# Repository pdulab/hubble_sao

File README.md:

## Features

The main features of the SAO are :
- An optical sensor : a VEML3328 to provide a 1x1 pixel RGB+IR camera
- An IMU (accel + gyro) : an LSM6DSO, because every good telescope needs to know its orientation (note that only one remaining gyroscope is working correctly on Hubble, so my SAO has the same number of gyroscope, nice !)
- 4 photodiodes : they represent the solar panels of Hubble. I'm using BPW34s (the IR version, to be precise). They are wired to the ADC of the microcontroller.
- An IR LED : to provide a way to send wireless data
- An microcontroller : I used a ATmega328PB

On top of that, there are :

- A standard yellow LED, because an SAO would be nothing without some blinky LEDs
- A button

## License
 Hubble SAO by pdulab is licensed under CC BY-NC-SA 4.0 

 ## Disclaimer
 This is a project for fun. I do not guarantee anything about it.
 The author is not affiliated with the official Hubble Space Telescope project or endorsed by it (or any related organization) in any way whatsoever.

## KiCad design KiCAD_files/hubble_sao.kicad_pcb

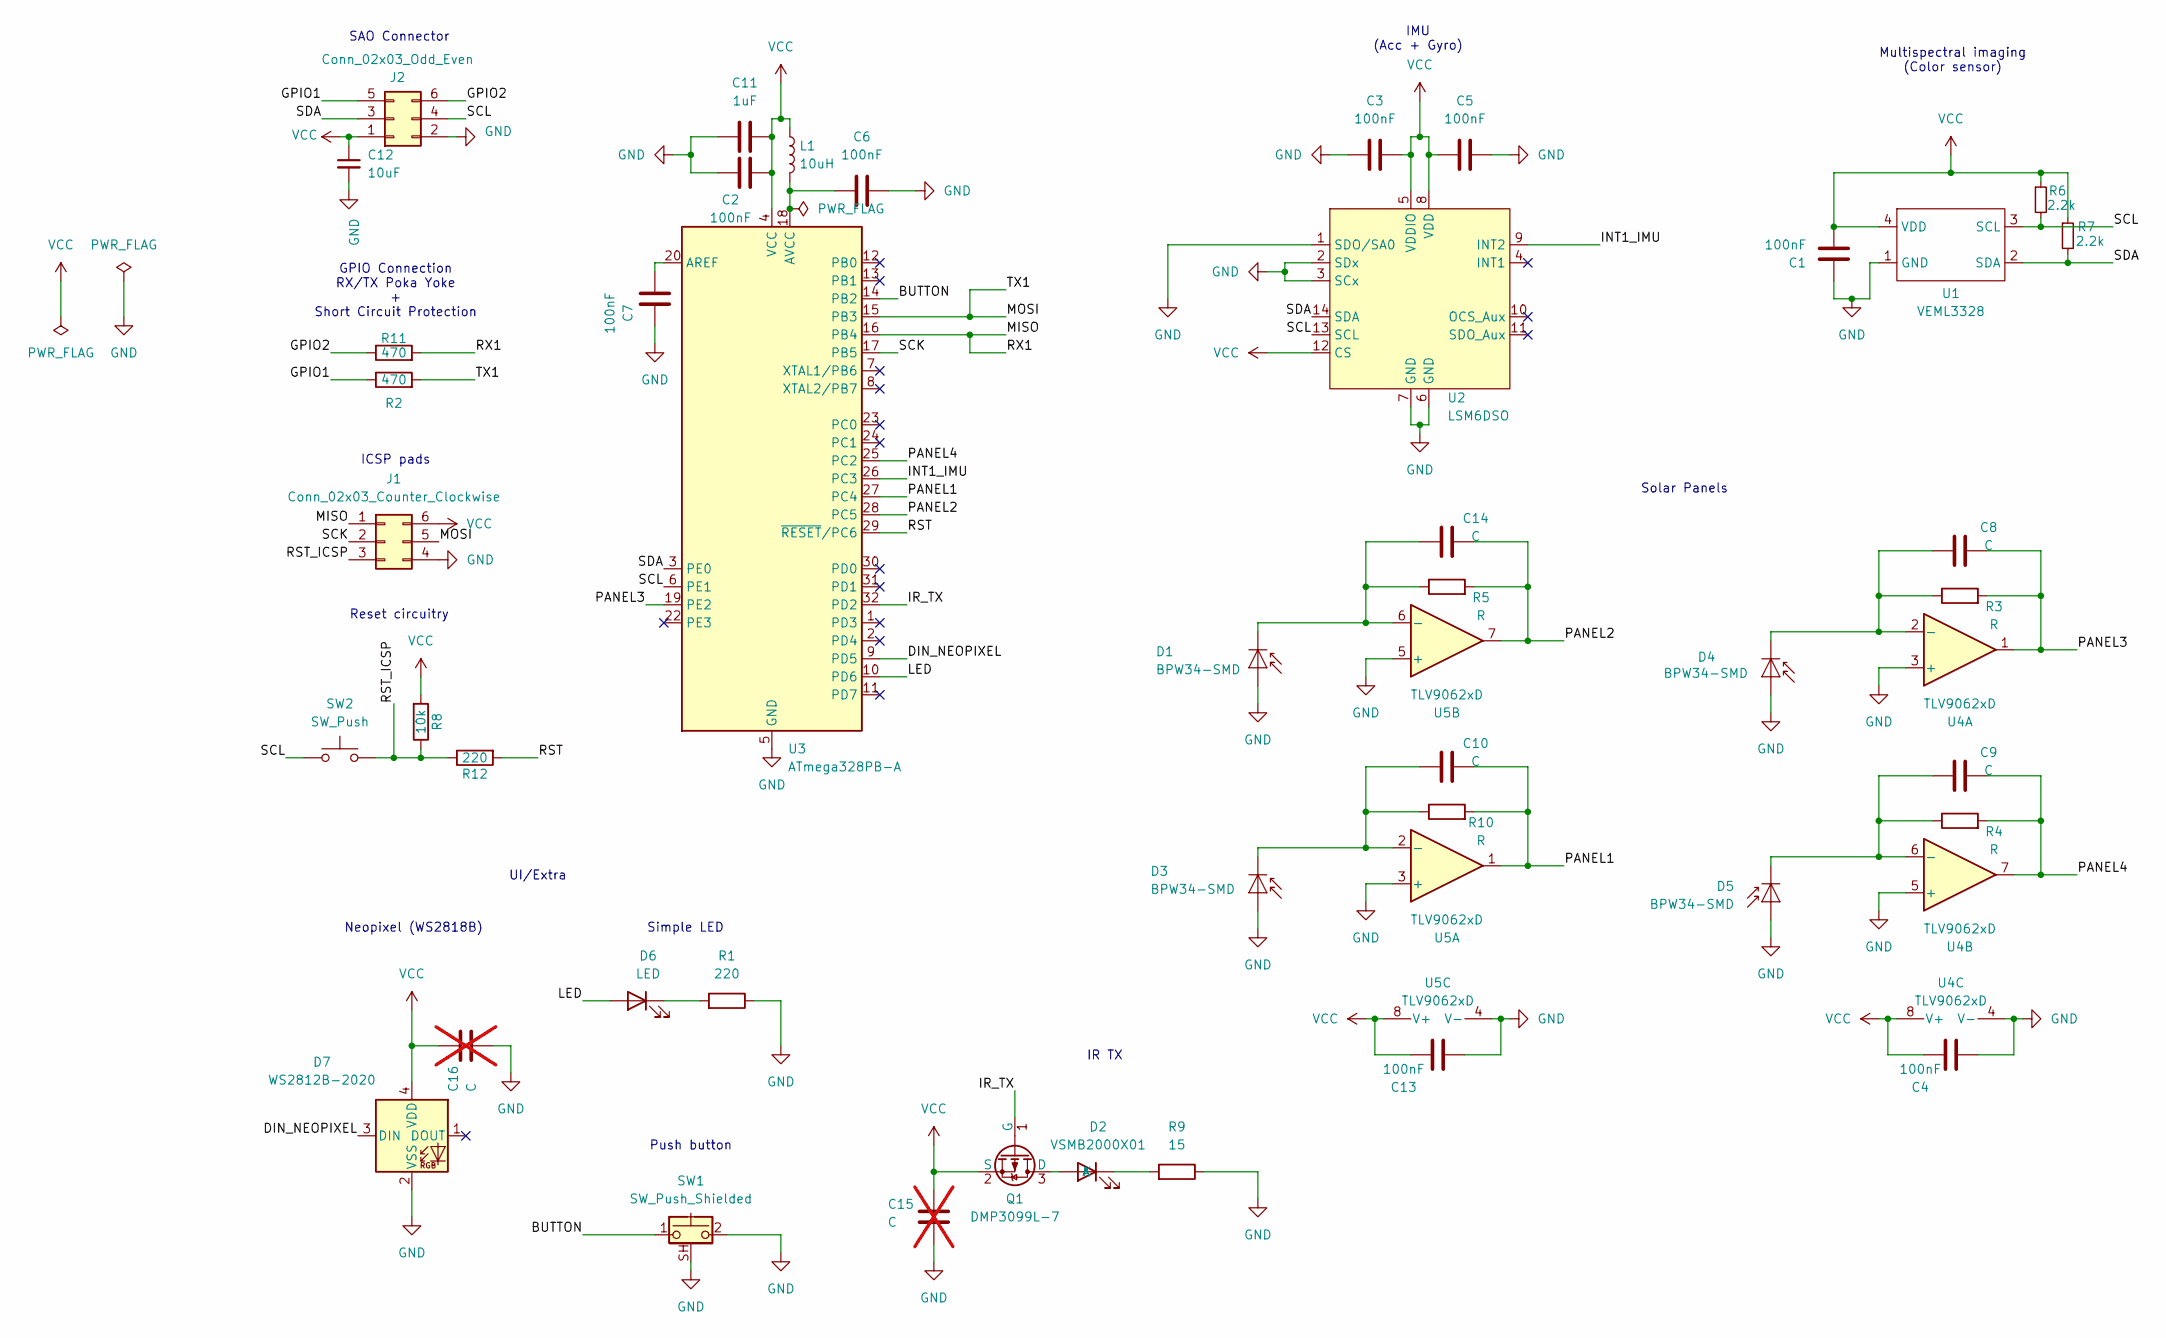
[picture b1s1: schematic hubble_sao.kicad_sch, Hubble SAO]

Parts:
C1, C2, C3, C4, C5, C6, C7, C13: 100nF; C_0805_2012Metric_Pad1.18x1.45mm_HandSolder
C8, C9, C10, C14: C; C_0805_2012Metric_Pad1.18x1.45mm_HandSolder
C11: 1uF; C_0805_2012Metric_Pad1.18x1.45mm_HandSolder
C12: 10uF; C_1206_3216Metric_Pad1.33x1.80mm_HandSolder
C15, C16: C; C_0603_1608Metric_Pad1.08x0.95mm_HandSolder; not fitted
D1, D3, D4, D5: BPW34-SMD; Osram_BPW34S-SMD
D2: VSMB2000X01; VxMx2000X01
D6: LED; LED_LiteOn_LTST-S110
D7: WS2812B-2020; LED_WS2812B-2020_PLCC4_2.0x2.0mm
J1: Conn_02x03_Counter_Clockwise; Pogo_pads_2x3_P2.54mm
J2: Conn_02x03_Odd_Even; PinHeader_2x03_P2.54mm_Vertical
L1: 10uH; L_0805_2012Metric_Pad1.15x1.40mm_HandSolder
Q1: DMP3099L-7; SOT-23
R1, R12: 220; R_0805_2012Metric_Pad1.20x1.40mm_HandSolder
R2, R11: 470; R_0805_2012Metric_Pad1.20x1.40mm_HandSolder
R3, R4, R5, R10: R; R_0805_2012Metric_Pad1.20x1.40mm_HandSolder
R6, R7: 2.2k; R_0805_2012Metric_Pad1.20x1.40mm_HandSolder
R8: 10k; R_0805_2012Metric_Pad1.20x1.40mm_HandSolder
R9: 15; R_1206_3216Metric_Pad1.30x1.75mm_HandSolder
SW1: SW_Push_Shielded; SW_SPST_B3U-1100P
SW2: SW_Push; SW_SPST_B3U-1000P
U1: VEML3328
U2: LSM6DSO; LGA-14_3x2.5mm_P0.5mm_LayoutBorder3x4y
U3: ATmega328PB-A; TQFP-32_7x7mm_P0.8mm
U4, U5: TLV9062xD; SOIC-8_3.9x4.9mm_P1.27mm

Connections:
/BUTTON: SW1.1, U3.14 (PB2)
/DIN_NEOPIXEL: D7.3 (DIN), U3.9 (PD5)
/GPIO1: J2.5, R2.1
/GPIO2: J2.6, R11.1
/INT1_IMU: U2.9 (INT2), U3.26 (PC3)
/IR_TX: Q1.1 (G), U3.32 (PD2)
/LED: D6.2 (A), U3.10 (PD6)
/MISO: J1.1, R11.2, U3.16 (PB4)
/MOSI: J1.5, R2.2, U3.15 (PB3)
/PANEL1: C10.2, R10.2, U3.27 (PC4), U5.1
/PANEL2: C14.2, R5.2, U3.28 (PC5), U5.7
/PANEL3: C8.2, R3.2, U3.19 (PE2), U4.1
/PANEL4: C9.2, R4.2, U3.25 (PC2), U4.7
/RST: R12.2, U3.29 (~RESET/PC6)
/RST_ICSP: J1.3, R8.1, R12.1, SW2.2
/SCK: J1.2, U3.17 (PB5)
/SCL: J2.4, R6.2, SW2.1, U1.3 (SCL), U2.13 (SCL), U3.6 (PE1)
/SDA: J2.3, R7.2, U1.2 (SDA), U2.14 (SDA), U3.3 (PE0)
GND: C1.1, C2.1, C3.2, C4.1, C5.2, C6.2, C7.1, C11.1, C12.2, C13.1, C15.2, C16.2, D1.2 (A), D3.2 (A), D4.2 (A), D5.2 (A), D7.2 (VSS), J1.4, J2.2, R1.1, R9.1, SW1.2, SW1.SH (B), U1.1 (GND), U2.1 (SDO/SA0), U2.2 (SDx), U2.3 (SCx), U2.6 (GND), U2.7 (GND), U3.5 (GND), U3.21 (GND), U4.3 (+), U4.4 (V-), U4.5 (+), U5.3 (+), U5.4 (V-), U5.5 (+)
unnamed: C14.1, D1.1 (K), R5.1, U5.6 (-)
unnamed: D2.2 (A), Q1.3 (D)
unnamed: D2.1 (K), R9.2
unnamed: C10.1, D3.1 (K), R10.1, U5.2 (-)
unnamed: C8.1, D4.1 (K), R3.1, U4.2 (-)
unnamed: C9.1, D5.1 (K), R4.1, U4.6 (-)
unnamed: D6.1 (K), R1.2
unnamed: C7.2, U3.20 (AREF)
unnamed: C6.1, L1.2, U3.18 (AVCC)
VCC: C1.2, C2.2, C3.1, C4.2, C5.1, C11.2, C12.1, C13.2, C15.1, C16.1, D7.4 (VDD), J1.6, J2.1, L1.1, Q1.2 (S), R6.1, R7.1, R8.2, U1.4 (VDD), U2.5 (VDDIO), U2.8 (VDD), U2.12 (CS), U3.4 (VCC), U4.8 (V+), U5.8 (V+)

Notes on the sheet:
Solar Panels
UI/Extra
IMU (Acc + Gyro)
Multispectral imaging (Color sensor)
IR TX
SAO Connector
Push button
Simple LED
Neopixel (WS2818B)
Reset circuitry
GPIO Connection RX/TX Poka Yoke + Short Circuit Protection
ICSP pads

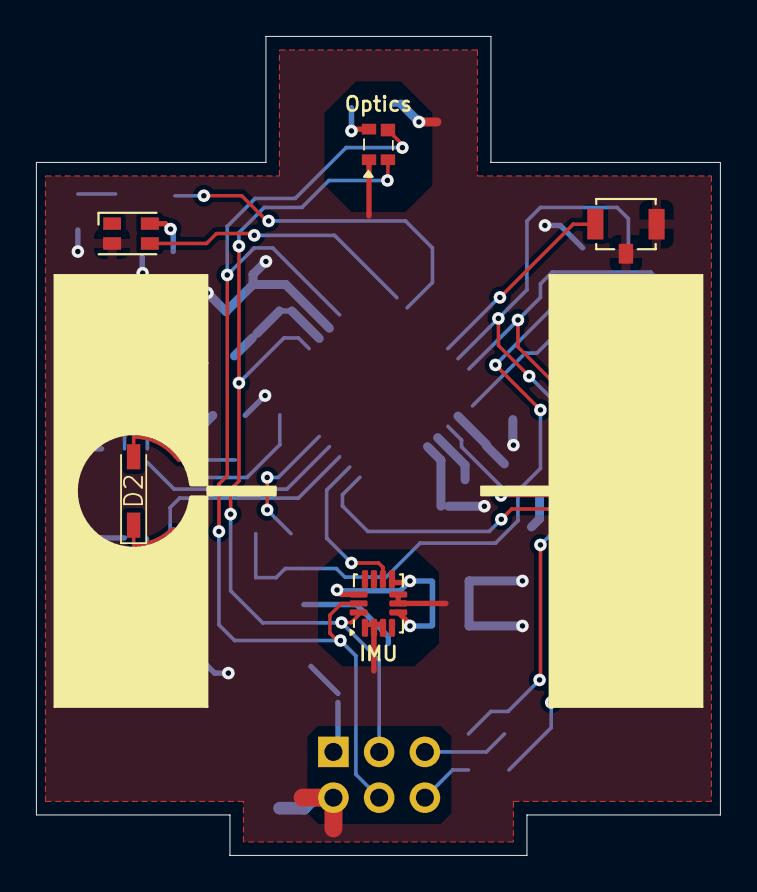
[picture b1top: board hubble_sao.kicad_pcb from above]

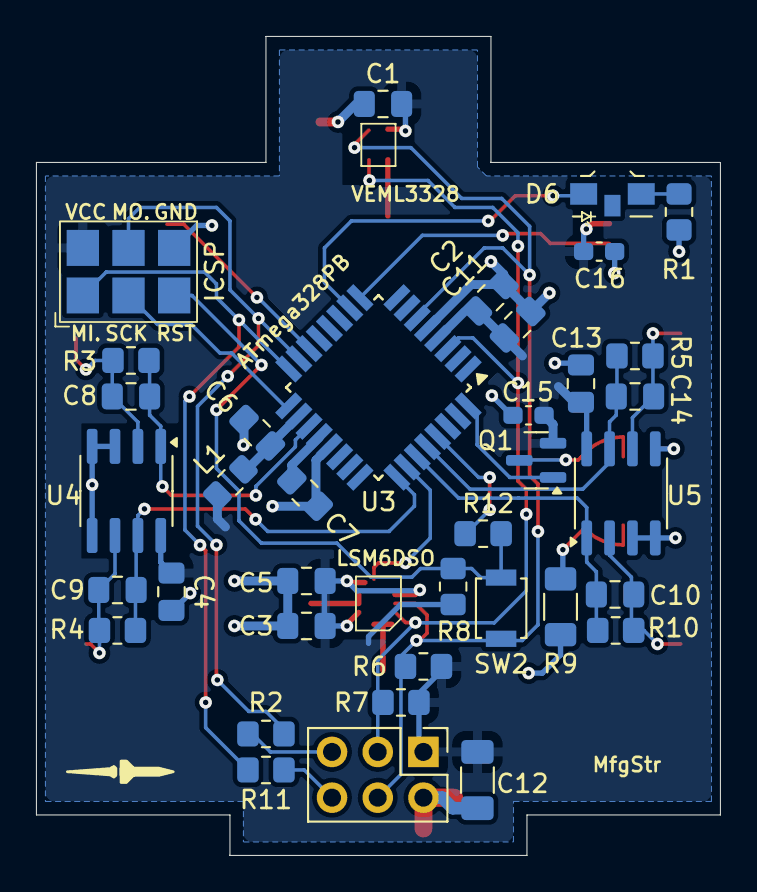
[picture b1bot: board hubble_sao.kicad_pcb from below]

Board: 2 copper layers, 38.0 x 45.5 mm, 46 parts (37 on the bottom side), 29 nets.

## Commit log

2025-02-03 Adding project files
2025-02-03 Updated .gitignore
2025-02-03 Corrected the input wiring of the opamps (schematic & pcb)
2025-02-03 Changed opamp from AD8532 to TLV9062D
2025-02-05 FIX: Corrected the pMOSFET wiring. Fixes #1
2025-02-05 Simplified the blinky LED's traces
2025-02-05 Fixed DRC errors
2025-02-08 Merged the front copper pours in a single ground plane
2025-02-08 Replaced some 1206 resistors by 0805s to tighten up the PCB
2025-02-08 Cleaned up the PCB around the IMU
2025-02-08 Renamed netclass VCC to Power. Included GND tracks to the new net class
2025-02-09 Replaced back GND plane/pour by a Power (VCC) plane/pour. Rerouted traces accordingly
2025-02-09 Cleaned up some traces
2025-02-22 Changed RX/TX resistors to 470Ohm for short circuit protection
    Fixes #4
2025-02-22 Created keep out around pin header
    - To enhance hand soldering (hopefully)
    - To still have soldermask instead of bare FR4 (was not the case before)
2025-02-24 Moved ICSP pads for an easier pogo pins positionning
    The ICSP pads are now positionned to be approx 0.1" and 0.2" from
    the board's sides. This means that alignement pins on a 0.1" grid
    can be used on the pogrammer's side to accurately position the
    pogo pins while programming. See User1 Layer for more info.
2025-02-24 Changed the manufacturer string/id to a default one
2025-02-25 Modified RESET circuitry
    - Added a switch to multiplex RESET and SCL on the pin header
    - Added short-circuit protection on the RESET pin
    - Added missing pullup resistor on the RESET pin. Before, RESET
    was left floating. No problem was noticed on the prototype.
2025-02-26 Moved Panel3 to 19/PE2/ADC6/ICP3
    This should enable the use of the Input Capture Pin 3.
2025-02-26 Reworked IR_TX LED
    - Removed the copper pour keep out and round copper traces (they
    were supposed too look nice, but in fact were not really visible)
    - Simplified the routing of the power around the MOSFET
2025-02-26 Added decoupling cap for the IR_TX LED (DNP for now) and touched up some tracks around there
2025-02-27 Fixed the silkscreen
2025-02-27 Modified blinky LEDs
    - Changed reverse mount LED for a side view LED
    - Added a WS2812N (Neopixel)
2025-02-27 Fixed some silkscreen
2025-02-27 A little bit of cleanup and verifications
2025-02-27 Touched up the schematic
2025-02-27 Updated version number to 2.0 and metadata
